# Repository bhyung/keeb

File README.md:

Wings.

Just a fun custom keyboard project
Ergo split with numpad, arrow cluster, and rotary encoder
Looks like wings!

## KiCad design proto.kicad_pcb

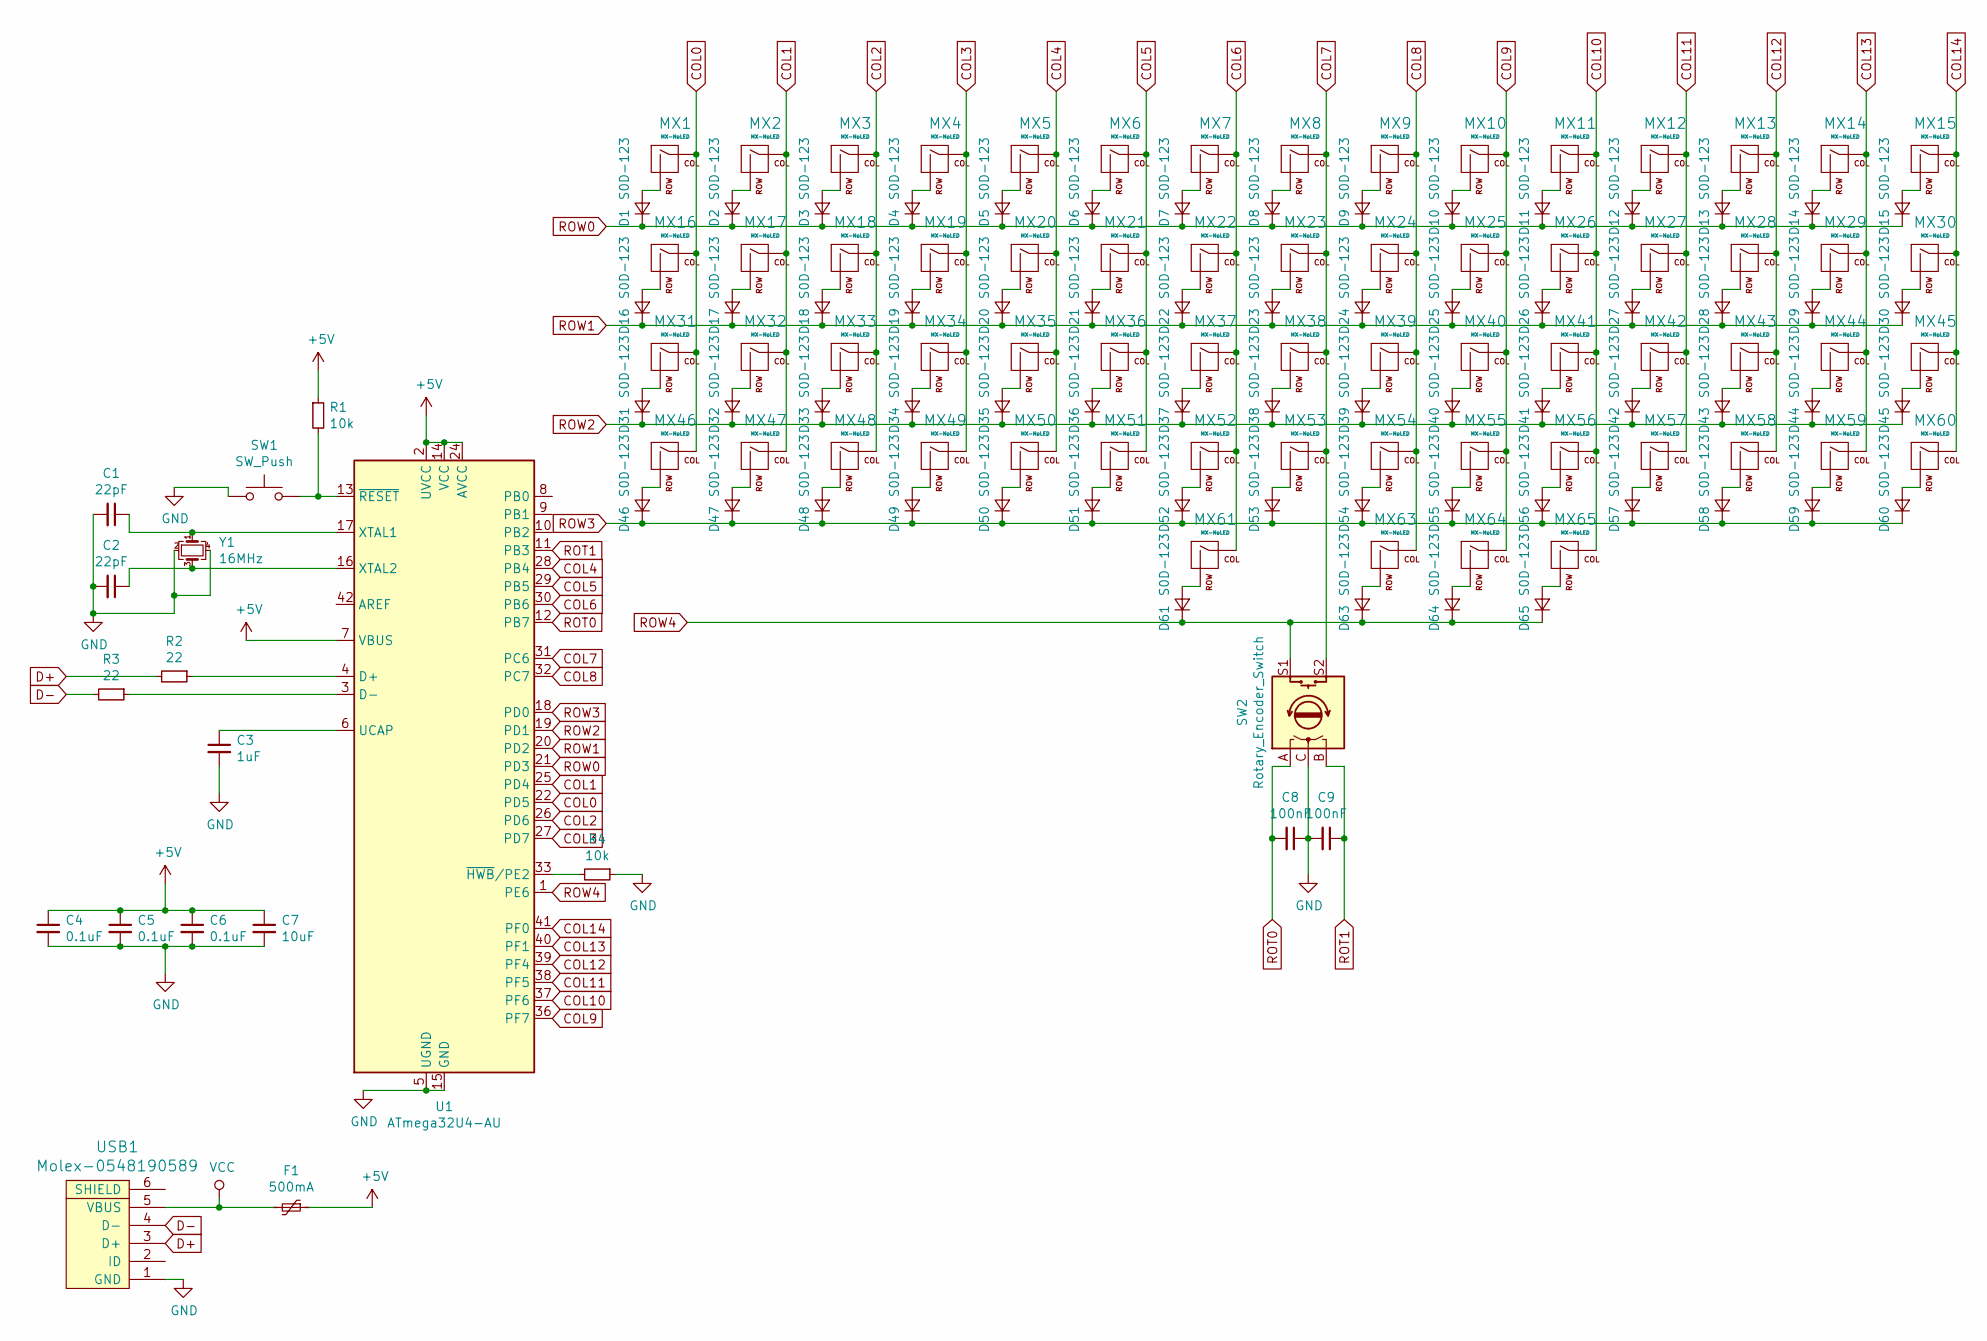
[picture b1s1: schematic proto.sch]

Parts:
C1, C2: 22pF; C_0805_2012Metric
C3: 1uF; C_0805_2012Metric
C4, C5, C6: 0.1uF; C_0805_2012Metric
C7: 10uF; C_0805_2012Metric
C8, C9: 100nF; C_0805_2012Metric
D1, D2, D3, D4, D5, D6, D7, D8, D9, D10, D11, D12, D13, D14, D15, D16, D17, D18, D19, D20, D21, D22, D23, D24, D25, D26, D27, D28, D29, D30, D31, D32, D33, D34, D35, D36, D37, D38, D39, D40, D41, D42, D43, D44, D45, D46, D47, D48, D49, D50, D51, D52, D53, D54, D55, D56, D57, D58, D59, D60, D61, D63, D64, D65: S0D-123; D_SOD-123
F1: 500mA; Fuse_1206_3216Metric
MX1, MX2, MX3, MX4, MX5, MX6, MX7, MX8, MX9, MX10, MX11, MX12, MX13, MX14, MX15, MX16, MX17, MX18, MX19, MX20, MX21, MX22, MX23, MX24, MX25, MX26, MX27, MX28, MX29, MX30, MX31, MX32, MX33, MX34, MX35, MX36, MX37, MX38, MX39, MX40, MX41, MX42, MX43, MX44, MX45, MX46, MX47, MX48, MX49, MX50, MX51, MX52, MX53, MX54, MX55, MX56, MX57, MX58, MX59, MX60, MX61, MX63, MX64, MX65: MX-NoLED; MX-1U
R1, R4: 10k; R_0805_2012Metric
R2, R3: 22; R_0805_2012Metric
SW1: SW_Push; SKQG-1155865
SW2: Rotary_Encoder_Switch; RotaryEncoder_Alps_EC11E-Switch_Vertical_H20mm
U1: ATmega32U4-AU; TQFP-44_10x10mm_P0.8mm
USB1: Molex-0548190589
Y1: 16MHz; Crystal_SMD_3225-4Pin_3.2x2.5mm

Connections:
+5V: C4.1, C5.1, C6.1, C7.1, F1.1, R1.1, U1.2 (UVCC), U1.7 (VBUS), U1.14 (VCC), U1.24 (AVCC), U1.34 (VCC), U1.44 (AVCC)
COL0: MX1.1 (COL), MX16.1 (COL), MX31.1 (COL), MX46.1 (COL), U1.22 (PD5)
COL1: MX2.1 (COL), MX17.1 (COL), MX32.1 (COL), MX47.1 (COL), U1.25 (PD4)
COL2: MX3.1 (COL), MX18.1 (COL), MX33.1 (COL), MX48.1 (COL), U1.26 (PD6)
COL3: MX4.1 (COL), MX19.1 (COL), MX34.1 (COL), MX49.1 (COL), U1.27 (PD7)
COL4: MX5.1 (COL), MX20.1 (COL), MX35.1 (COL), MX50.1 (COL), U1.28 (PB4)
COL5: MX6.1 (COL), MX21.1 (COL), MX36.1 (COL), MX51.1 (COL), U1.29 (PB5)
COL6: MX7.1 (COL), MX22.1 (COL), MX37.1 (COL), MX52.1 (COL), MX61.1 (COL), U1.30 (PB6)
COL7: MX8.1 (COL), MX23.1 (COL), MX38.1 (COL), MX53.1 (COL), SW2.S2, U1.31 (PC6)
COL8: MX9.1 (COL), MX24.1 (COL), MX39.1 (COL), MX54.1 (COL), MX63.1 (COL), U1.32 (PC7)
COL9: MX10.1 (COL), MX25.1 (COL), MX40.1 (COL), MX55.1 (COL), MX64.1 (COL), U1.36 (PF7)
COL10: MX11.1 (COL), MX26.1 (COL), MX41.1 (COL), MX56.1 (COL), MX65.1 (COL), U1.37 (PF6)
COL11: MX12.1 (COL), MX27.1 (COL), MX42.1 (COL), MX57.1 (COL), U1.38 (PF5)
COL12: MX13.1 (COL), MX28.1 (COL), MX43.1 (COL), MX58.1 (COL), U1.39 (PF4)
COL13: MX14.1 (COL), MX29.1 (COL), MX44.1 (COL), MX59.1 (COL), U1.40 (PF1)
COL14: MX15.1 (COL), MX30.1 (COL), MX45.1 (COL), MX60.1 (COL), U1.41 (PF0)
D+: R2.2, USB1.3 (D+)
D-: R3.2, USB1.4 (D-)
GND: C1.2, C2.2, C3.2, C4.2, C5.2, C6.2, C7.2, C8.1, C9.2, R4.1, SW1.1, SW2.C, U1.5 (UGND), U1.15 (GND), U1.23 (GND), U1.35 (GND), U1.43 (GND), USB1.1 (GND), Y1.2, Y1.4
unnamed: C1.1, U1.17 (XTAL1), Y1.1
unnamed: C2.1, U1.16 (XTAL2), Y1.3
unnamed: C3.1, U1.6 (UCAP)
unnamed: D1.2 (A), MX1.2 (ROW)
unnamed: D2.2 (A), MX2.2 (ROW)
unnamed: D3.2 (A), MX3.2 (ROW)
unnamed: D4.2 (A), MX4.2 (ROW)
unnamed: D5.2 (A), MX5.2 (ROW)
unnamed: D6.2 (A), MX6.2 (ROW)
unnamed: D7.2 (A), MX7.2 (ROW)
unnamed: D8.2 (A), MX8.2 (ROW)
unnamed: D9.2 (A), MX9.2 (ROW)
unnamed: D10.2 (A), MX10.2 (ROW)
unnamed: D11.2 (A), MX11.2 (ROW)
unnamed: D12.2 (A), MX12.2 (ROW)
unnamed: D13.2 (A), MX13.2 (ROW)
unnamed: D14.2 (A), MX14.2 (ROW)
unnamed: D15.2 (A), MX15.2 (ROW)
unnamed: D16.2 (A), MX16.2 (ROW)
unnamed: D17.2 (A), MX17.2 (ROW)
unnamed: D18.2 (A), MX18.2 (ROW)
unnamed: D19.2 (A), MX19.2 (ROW)
unnamed: D20.2 (A), MX20.2 (ROW)
unnamed: D21.2 (A), MX21.2 (ROW)
unnamed: D22.2 (A), MX22.2 (ROW)
unnamed: D23.2 (A), MX23.2 (ROW)
unnamed: D24.2 (A), MX24.2 (ROW)
unnamed: D25.2 (A), MX25.2 (ROW)
unnamed: D26.2 (A), MX26.2 (ROW)
unnamed: D27.2 (A), MX27.2 (ROW)
unnamed: D28.2 (A), MX28.2 (ROW)
unnamed: D29.2 (A), MX29.2 (ROW)
unnamed: D30.2 (A), MX30.2 (ROW)
unnamed: D31.2 (A), MX31.2 (ROW)
unnamed: D32.2 (A), MX32.2 (ROW)
unnamed: D33.2 (A), MX33.2 (ROW)
unnamed: D34.2 (A), MX34.2 (ROW)
unnamed: D35.2 (A), MX35.2 (ROW)
unnamed: D36.2 (A), MX36.2 (ROW)
unnamed: D37.2 (A), MX37.2 (ROW)
unnamed: D38.2 (A), MX38.2 (ROW)
unnamed: D39.2 (A), MX39.2 (ROW)
unnamed: D40.2 (A), MX40.2 (ROW)
unnamed: D41.2 (A), MX41.2 (ROW)
unnamed: D42.2 (A), MX42.2 (ROW)
unnamed: D43.2 (A), MX43.2 (ROW)
unnamed: D44.2 (A), MX44.2 (ROW)
unnamed: D45.2 (A), MX45.2 (ROW)
unnamed: D46.2 (A), MX46.2 (ROW)
unnamed: D47.2 (A), MX47.2 (ROW)
unnamed: D48.2 (A), MX48.2 (ROW)
unnamed: D49.2 (A), MX49.2 (ROW)
unnamed: D50.2 (A), MX50.2 (ROW)
unnamed: D51.2 (A), MX51.2 (ROW)
unnamed: D52.2 (A), MX52.2 (ROW)
unnamed: D53.2 (A), MX53.2 (ROW)
unnamed: D54.2 (A), MX54.2 (ROW)
unnamed: D55.2 (A), MX55.2 (ROW)
unnamed: D56.2 (A), MX56.2 (ROW)
unnamed: D57.2 (A), MX57.2 (ROW)
unnamed: D58.2 (A), MX58.2 (ROW)
unnamed: D59.2 (A), MX59.2 (ROW)
unnamed: D60.2 (A), MX60.2 (ROW)
unnamed: D61.2 (A), MX61.2 (ROW)
unnamed: D63.2 (A), MX63.2 (ROW)
unnamed: D64.2 (A), MX64.2 (ROW)
unnamed: D65.2 (A), MX65.2 (ROW)
unnamed: R1.2, SW1.2, U1.13 (~RESET)
unnamed: R2.1, U1.4 (D+)
unnamed: R3.1, U1.3 (D-)
unnamed: R4.2, U1.33 (~HWB~/PE2)
ROT0: C8.2, SW2.A, U1.12 (PB7)
ROT1: C9.1, SW2.B, U1.11 (PB3)
ROW0: D1.1 (K), D2.1 (K), D3.1 (K), D4.1 (K), D5.1 (K), D6.1 (K), D7.1 (K), D8.1 (K), D9.1 (K), D10.1 (K), D11.1 (K), D12.1 (K), D13.1 (K), D14.1 (K), D15.1 (K), U1.21 (PD3)
ROW1: D16.1 (K), D17.1 (K), D18.1 (K), D19.1 (K), D20.1 (K), D21.1 (K), D22.1 (K), D23.1 (K), D24.1 (K), D25.1 (K), D26.1 (K), D27.1 (K), D28.1 (K), D29.1 (K), D30.1 (K), U1.20 (PD2)
ROW2: D31.1 (K), D32.1 (K), D33.1 (K), D34.1 (K), D35.1 (K), D36.1 (K), D37.1 (K), D38.1 (K), D39.1 (K), D40.1 (K), D41.1 (K), D42.1 (K), D43.1 (K), D44.1 (K), D45.1 (K), U1.19 (PD1)
ROW3: D46.1 (K), D47.1 (K), D48.1 (K), D49.1 (K), D50.1 (K), D51.1 (K), D52.1 (K), D53.1 (K), D54.1 (K), D55.1 (K), D56.1 (K), D57.1 (K), D58.1 (K), D59.1 (K), D60.1 (K), U1.18 (PD0)
ROW4: D61.1 (K), D63.1 (K), D64.1 (K), D65.1 (K), SW2.S1, U1.1 (PE6)
VCC: F1.2, USB1.5 (VBUS)

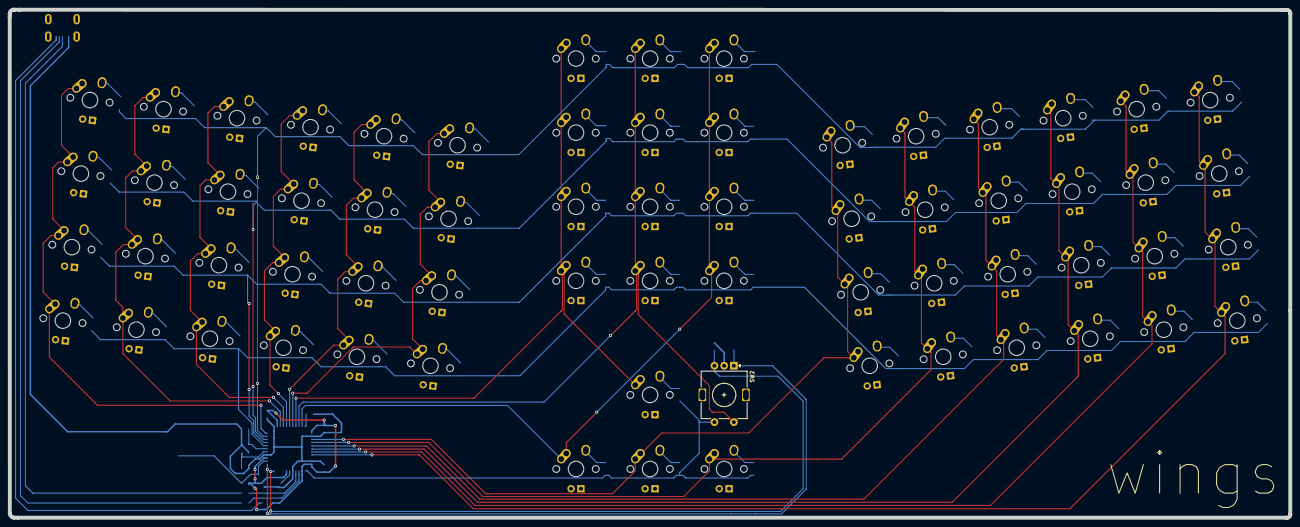
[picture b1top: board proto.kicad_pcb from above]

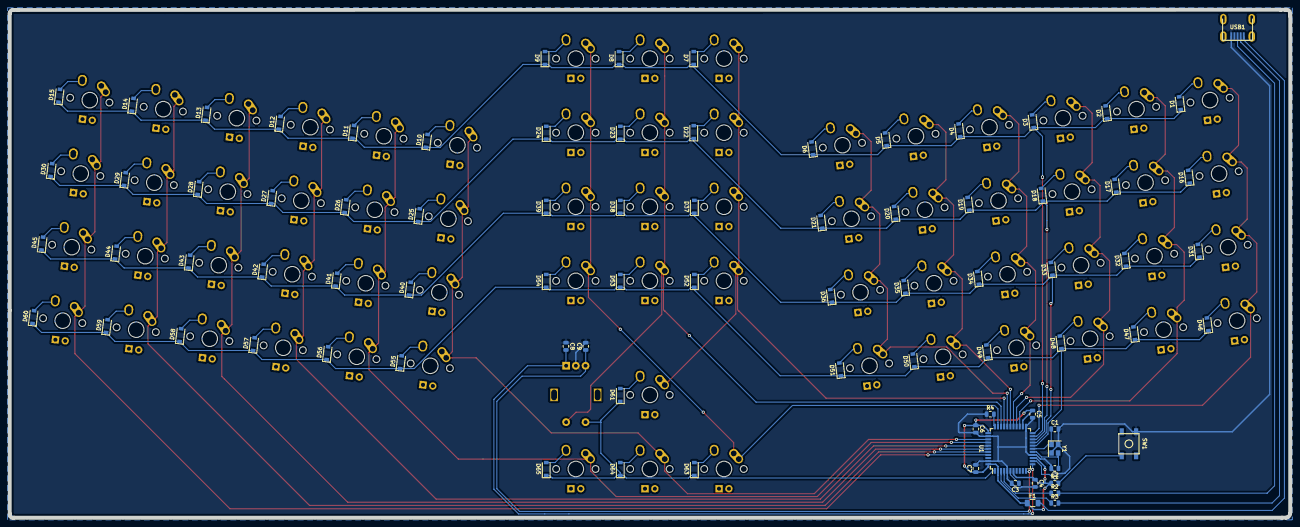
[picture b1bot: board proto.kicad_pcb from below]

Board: 2 copper layers, 329.3 x 130.6 mm, 147 parts (82 on the bottom side), 98 nets.

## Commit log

2021-01-14 create
2021-01-14 submodules
2021-01-14 configured libs
2021-01-14 schematic
2021-01-15 routing
2021-01-15 rotary
2021-01-15 layout
2021-01-16 edits
2021-01-16 edits proto
2021-01-22 plate stl, updated pcb
